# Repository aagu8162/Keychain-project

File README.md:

# Keychain-project

This repository holds the open-source hardware and firmware design files for my **Hack Club Half-Life** week 4 project submission. This project was done because I have wanted to build something like this.

This week my goal was to make a keychain with an oled display which would display words. I used Kicad to build the schematics and then finally built the pcb by referring to the oled guide and by also using my experience of building the week 1 project. There was not much customizations but I arranged it in a layout which I thought would make it more compact. I used the XIAO ESP32-C3 as my microcontoller and Arduino IDE was used for the firmware. The guide had provided libraries from where I could refer code and code my controller. I also added a rechargeable battery and a slide switch to turn it on or off.

## 📁 Repository Structure
* `/pcb` - KiCad schematics, layouts, and manufacturing outputs.
* `/firmware` - Arduino IDE configuration code files.

# **Schematic of PCB**

# **3D View**

## BUTTONS

**Button 1**: Allows to display different things as per the code

**Button 2**: On or off switch

# BOM(Bill of Materials)

|Item|Qty|Supplier|Cost/item|Total Cost|
|---|---|---|---|---|
|XIAO ESP32 C3|1|[Sharvi](https://sharvielectronics.com/product/seeed-studio-xiao-esp32c3-tiny-mcu-board-with-wifi-and-ble-battery-charge-supported-module/)|$6.70|$6.70|
|0.96 OLED|1|[Sharvi](https://sharvielectronics.com/product/0-96-inch-i2c-4pin-oled-display-module-white/)|$2.20|$2.20|
|3.7V Lipo Rechargeable|1|[Sharvi](https://sharvielectronics.com/product/3-7v-1100mah-lipo-rechargeable-battery-with-jst-ph-2mm-connector/)|$2.28|$2.28|
|4.7K Ohm Resitstors|2|[Sharvi](https://sharvielectronics.com/product/4-7k-ohm-1-8-watt-resistor-1-tolerance-cr-05ftp-4k7-0805-package/)|$0.085|$0.17|
|100nF 50V Capacitor|1|[Sharvi](https://sharvielectronics.com/product/0-1uf-100nf-50v-capacitor-%c2%b110-tolerance-cc0805kkx7r9bb104-0805-package/)|$0.021|$0.021|
|10uF/10000nF 25V Capacitor|1|[Sharvi](https://sharvielectronics.com/product/10uf-10000nf-25v-capacitor-%c2%b110-tolerance-cc0805kkx7r8bb106-0805-package/)|$0.029|$0.029|
|Push Button|3|[Sharvi](https://sharvielectronics.com/product/6x6x6mm-4-pin-smd-push-button-switch-black-smd-package/)|$0.093|$0.279|
|Slide Switch|1|[Sharvi](https://sharvielectronics.com/product/mini-slide-switch-7pin-smd-2-positions-h1-5mm-1p2t-spdt/)|$0.63|$0.63|
|4Pin Female Berg Strip|1|[Sharvi](https://sharvielectronics.com/product/4x1-4pin-female-berg-strip-break-away-header-straight-2-54mm-pitch/)|$0.66|$0.66|
|2Pin SMD Horizontal Connector|1|[Sharvi](https://sharvielectronics.com/product/ph-02awt-2pin-smd-horizontal-connector-with-side-entry-header-2mm-pitch/)|$0.41|$0.41|
|PCB|1|[Seeed Studio](https://www.seeedstudio.com/fusion_pcb.html)|$9.90|$9.90|
|Estimated total shipping||||$7.41|

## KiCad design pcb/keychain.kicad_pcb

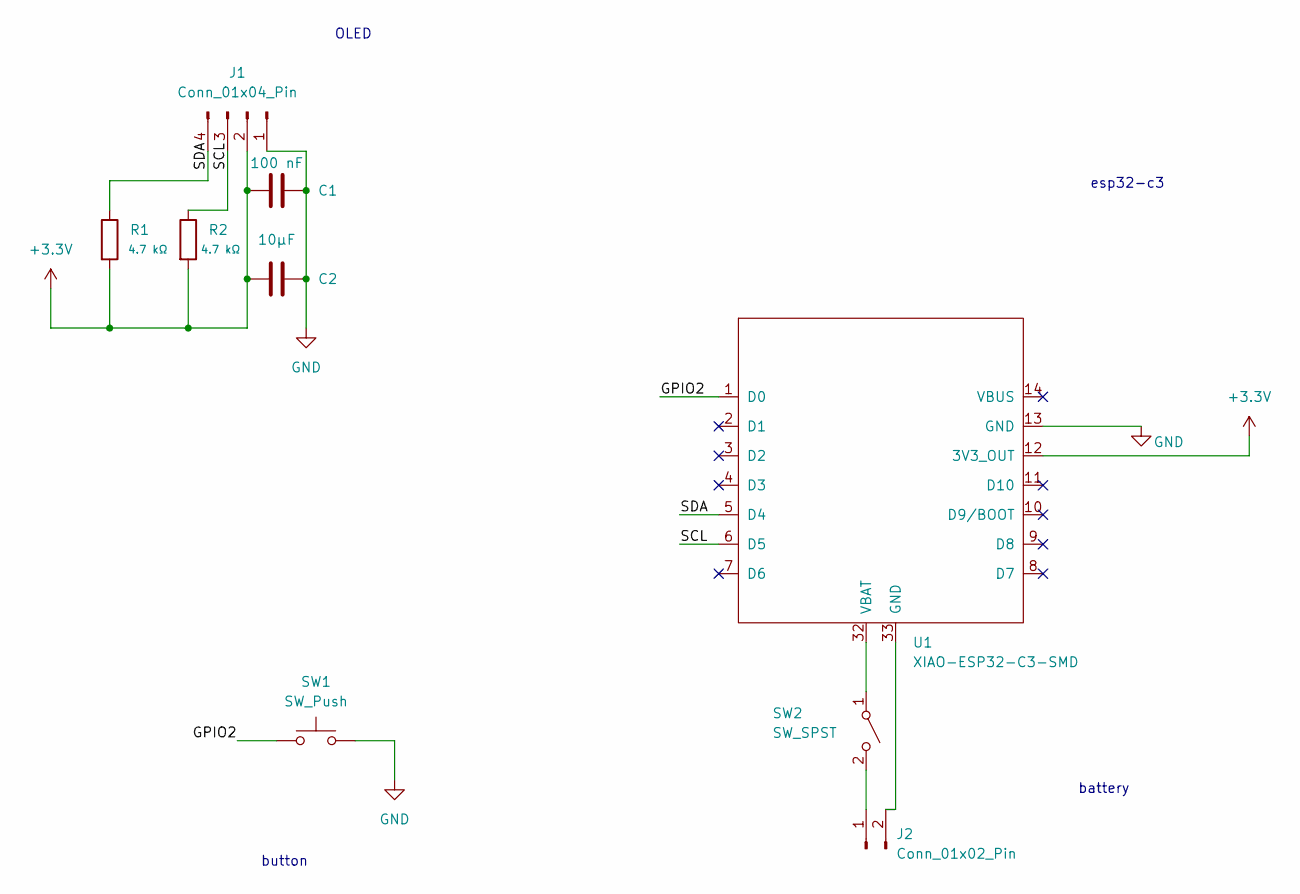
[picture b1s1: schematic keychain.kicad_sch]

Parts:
C1: 100 nF; C_0805_2012Metric
C2: 10µF; C_0805_2012Metric
J1: Conn_01x04_Pin; PinSocket_1x04_P2.54mm_Vertical
J2: Conn_01x02_Pin; JST_PH_S2B-PH-K_1x02_P2.00mm_Horizontal
R1, R2: 4.7 kΩ; R_0805_2012Metric
SW1: SW_Push; SW_SPST_PTS645Sx43SMTR92
SW2: SW_SPST; SW_SPDT_Shouhan_MSK12C02
U1: XIAO-ESP32-C3-SMD

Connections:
+3.3V: C1.1, C2.1, J1.2, R1.2, R2.2, U1.12 (3V3_OUT)
/GPIO2: SW1.1, U1.1 (D0)
/SCL: J1.3, R2.1, U1.6 (D5)
/SDA: J1.4, R1.1, U1.5 (D4)
GND: C1.2, C2.2, J1.1, SW1.2, U1.13 (GND)
unnamed: J2.1, SW2.2 (B)
unnamed: J2.2, U1.33 (GND)
unnamed: SW2.1 (A), U1.32 (VBAT)

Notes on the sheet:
esp32-c3
OLED
battery
button

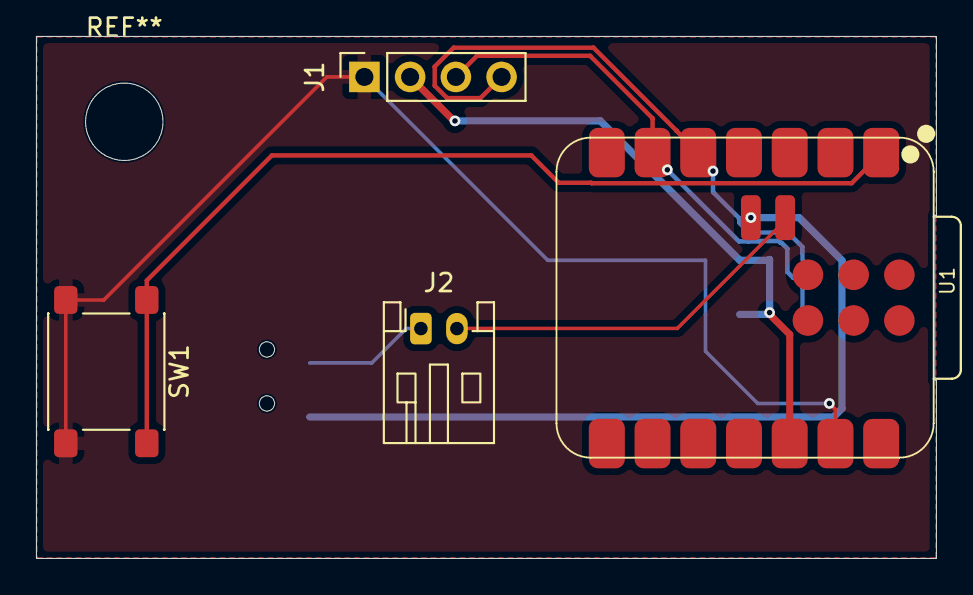
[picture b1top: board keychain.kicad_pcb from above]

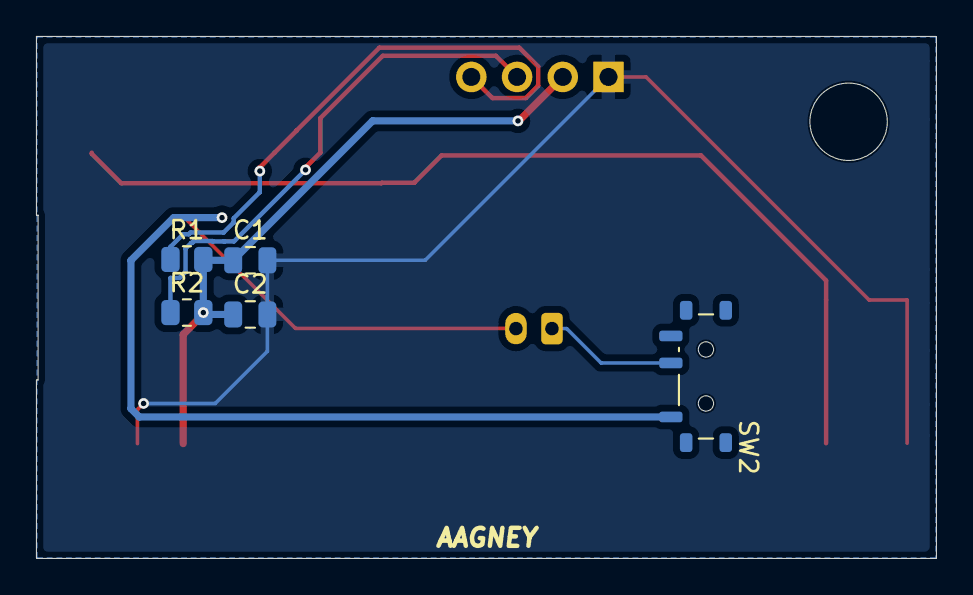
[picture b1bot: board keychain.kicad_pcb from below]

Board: 2 copper layers, 50.0 x 29.0 mm, 9 parts (5 on the bottom side), 8 nets.
